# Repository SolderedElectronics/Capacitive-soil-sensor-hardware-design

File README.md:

# Capacitive soil sensor Hardware Design

## About the Product

|  |
| :----------------------------------------------------------: |
| [Buy Capacitive soil sensor](https://www.solde.red/333098) |

How many times have you watered your plants and feared you overdid it? With the capacitive soil sensor, those worries are a thing of the past!

Most cheap soil sensors work on the resistance principle, where there are two prongs and the sensor measures the conductivity between them. They work fine at first, but eventually begin to oxidize due to the exposed metal. Even if they are gold plated! Due to oxidation, the resistance goes up and up, so you have to constantly recalibrate your code. Also, resistance measurements do not always work in loose soil.

This design with capacitive measurement is superior. Capacitive measurements use only one prong, have no exposed metal, and do not introduce direct current into your plants.

---

## Repository Contents

This repository contains all design files for Capacitive soil sensor, organized as follows:

- **`CAD` folder**: Contains KiCAD design files, including:
  - Schematics
  - PCB layout
  - Panel PCB layout
  - Source 3D files in Fusion360, if any
  - All files are sorted by version with a detailed change log.
- **`OUTPUTS` folder**: Includes all production-ready files, such as:
  - Bill of Materials (BOM) and interactive BOM (iBOM)
  - PDF versions of schematics
  - 3D `.step` file of the board
  - 3D-printable models
  - Gerber files for PCB manufacturing
  - Image of the pinout of the board
  - Product image
  - Compliance, legal and generic sales documents

Refer to the `Change Log` in the CAD folder for details about updates between versions.

---

## Learn More About the Product

Beyond the repository, explore the following resources:

### Soldered Verify

The **Soldered Verify** system ensures every board you purchase from Soldered is fully functional. It also provides access to exclusive test data for your product. To get started, find the unique Soldered Verify ID on your product's packaging and enter the ID on the [Soldered Verify page](https://soldered.com/verify/) to access test results and additional product details.

### Soldered Community

Soldered Community is your go-to place for technical support. Our engineers track and answer all questions posted there, and it’s a great space for the maker community. Get answers to your questions and solutions for your challenges at [Soldered Community](https://soldered.com/community).

### solde.red

solde.red is an ultimate URL shortener and information hub. Access it by typing solde.red/ followed by your product SKU, e.g., [solde.red/333000](https://solde.red/333000), to find getting-started guides, datasheets, open-source hardware and software files, certifications, images, pinouts, and more. Read more about the shortener [here](https://solde.red/info/).

---

## Contributing

Contributions are welcome! Here’s how you can get involved:

- Submit pull requests to enhance the design or fix issues.
- Report bugs or problems by opening an issue.

We encourage community collaboration to make this product even better.

---

## About Soldered

[Soldered for Makers](https://soldered.com) specializes in designing and manufacturing electronic products tailored for enthusiasts, ranging from hobbyists to professionals. Our portfolio includes electronic boards, sensors, and actuators that are widely utilized in fields such as microelectronics, mechatronics, robotics, programming, and IoT. Every product we offer is designed in-house and built upon open-source hardware and software platforms. Proudly certified and manufactured within the European Union, our catalog likely includes the product you need for your project.

We complement these products with comprehensive tutorials and manuals, product descriptions, schematics, programming codes, and project examples. Our round-the-clock [customer and technical support](https://soldered.com/community) is available for all our products, irrespective of the sales channel. Soldered’s success and services reflect our maker community’s unwavering [trust](https://www.trustpilot.com/review/soldered.com), for which we are deeply grateful. Join our community and create using Soldered products.

---

## License

All Soldered open-source hardware (OSH) is under The TAPR Open Hardware License. Read more in the LICENSE file located in this repository.

**Disclaimer:**

No warranty - all designs in this repository are distributed in the hope that they will be useful, but without any warranty. They are provided "AS IS", therefore without warranty of any kind, either expressed or implied. The entire quality and performance of what you do with the contents of this repository are your responsibility. In no event Soldered Electronics will be liable for your damages, or losses, including any general, special, incidental, or consequential damage arising out of the use or inability to use the contents of this repository. 

---

## Have fun!

Thank you for your support from your fellow makers at Soldered Electronics.

Happy Making!

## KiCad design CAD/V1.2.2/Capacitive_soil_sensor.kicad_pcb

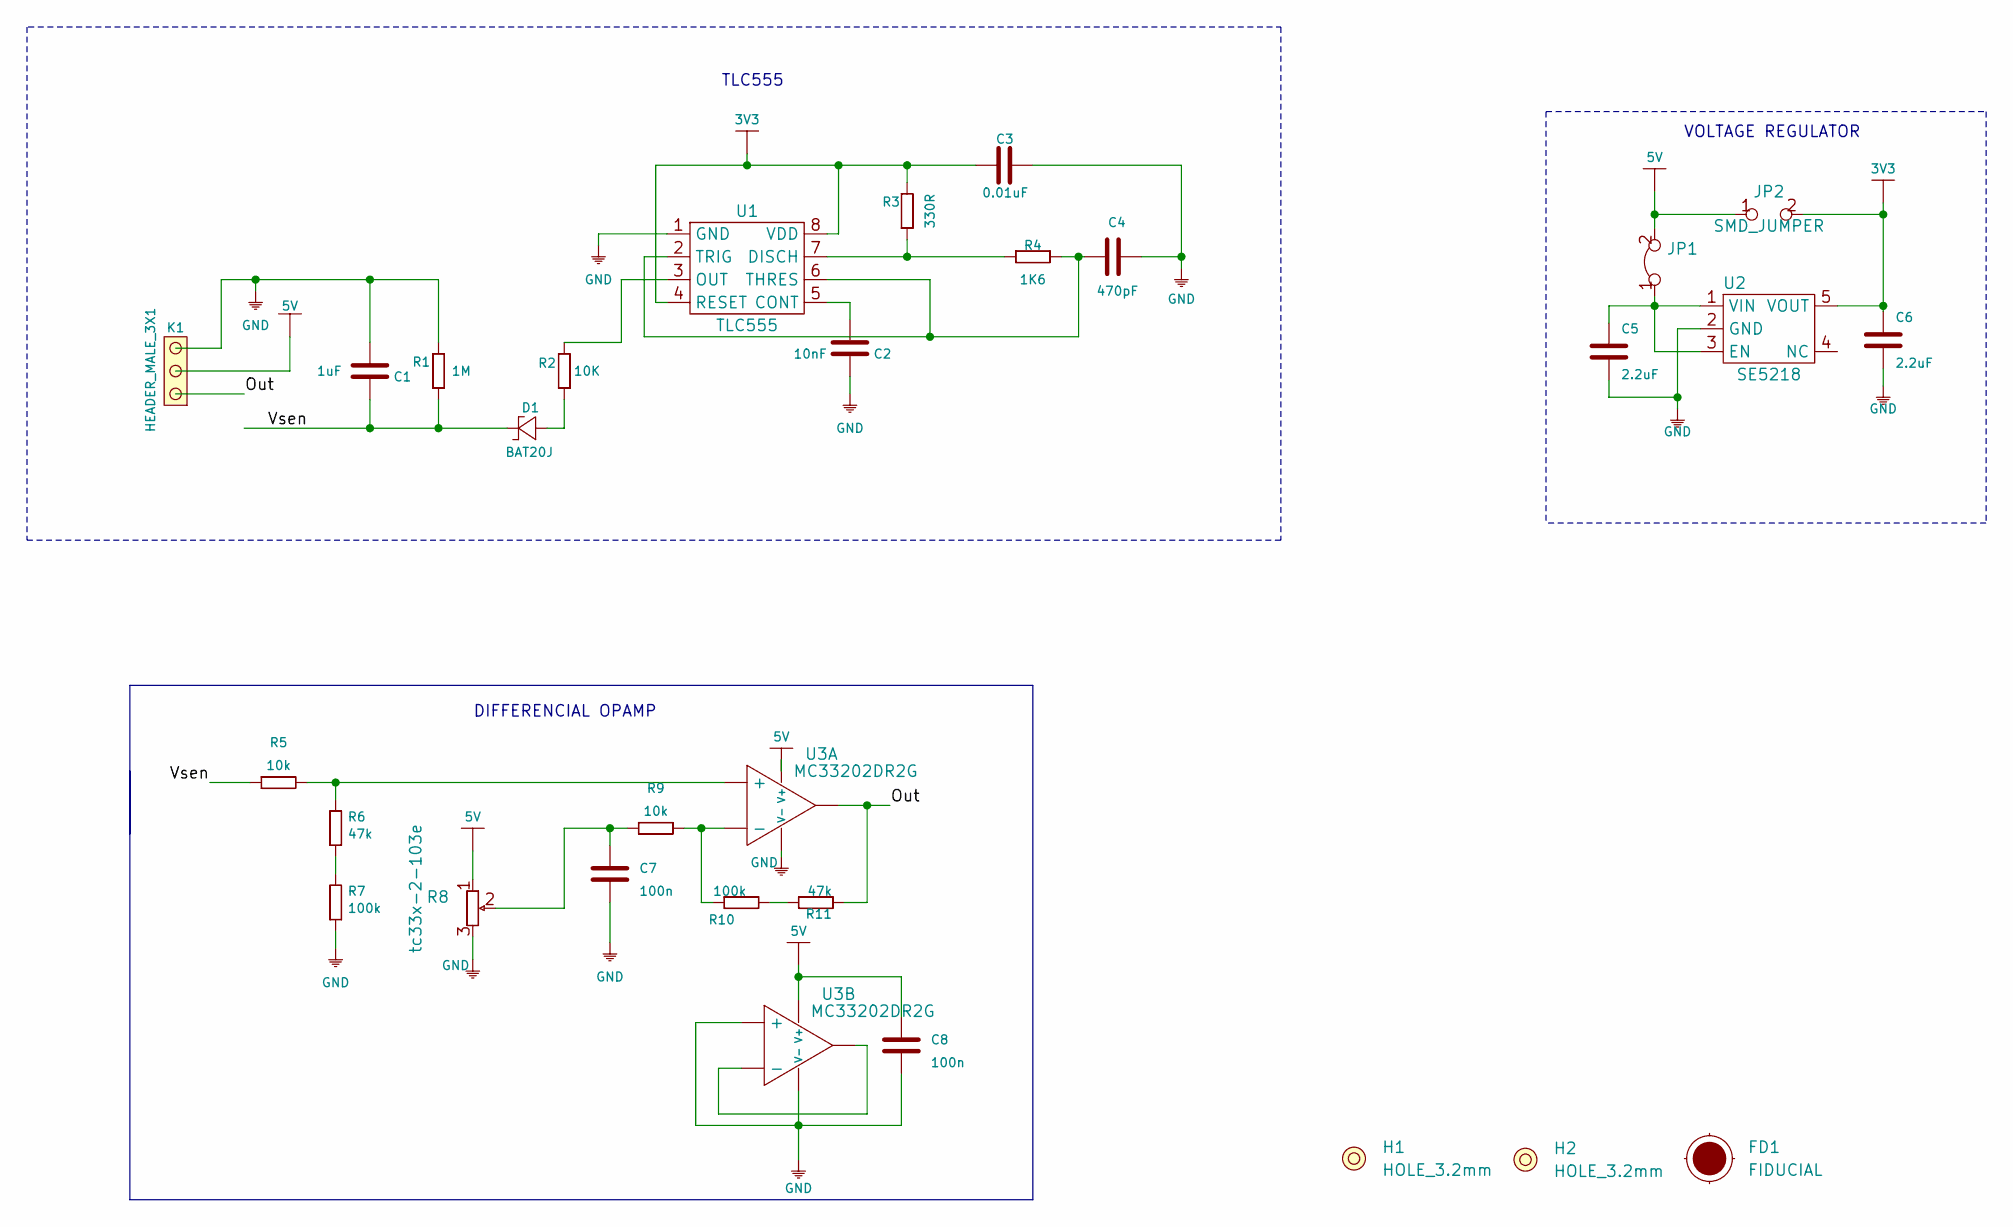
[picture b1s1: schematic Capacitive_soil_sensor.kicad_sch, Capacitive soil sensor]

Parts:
C1: 1uF; 0603C
C2: 10nF; 0603C
C3: 0.01uF; 0603C
C4: 470pF; 0603C
C5, C6: 2.2uF; 0603C
C7, C8: 100n; 0603C
D1: BAT20J; SOD-323
FD1: FIDUCIAL; FIDUCIAL_23
H1, H2: HOLE_3.2mm
JP1: SMD-JUMPER-CONNECTED_TRACE_SLODERMASK
JP2: SMD_JUMPER
K1: HEADER_MALE_3X1
R1: 1M; 0603R
R2: 10K; 0603R
R3: 330R; 0603R
R4: 1K6; 0603R
R5, R9: 10k; 0603R
R6, R11: 47k; 0603R
R7, R10: 100k; 0603R
R8: tc33x-2-103e
U1: TLC555; SOIC−8
U2: SE5218; SOT-23-5
U3: MC33202DR2G; SOIC−8

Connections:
3V3: C3.2, C6.2, JP2.2, R3.2, U1.4 (RESET), U1.8 (VDD), U2.5 (VOUT)
5V: C8.1, JP1.2, JP2.1, K1.2, R8.1, U3.8 (V+)
/Out: K1.1, R11.2, U3.1
/Vsen: C1.1, D1.2 (K), R1.1, R5.1
GND: C1.2, C2.1, C3.1, C4.1, C5.1, C6.1, C7.2, C8.2, K1.3, R1.2, R7.1, R8.3, U1.1 (GND), U2.2 (GND), U3.4 (V-), U3.5 (+)
unnamed: C2.2, U1.5 (CONT)
unnamed: C4.2, R4.2, U1.2 (TRIG), U1.6 (THRES)
unnamed: C5.2, JP1.1, U2.1 (VIN), U2.3 (EN)
unnamed: C7.1, R8.2, R9.1
unnamed: D1.1 (A), R2.1
unnamed: R2.2, U1.3 (OUT)
unnamed: R3.1, R4.1, U1.7 (DISCH)
unnamed: R5.2, R6.2, U3.3 (+)
unnamed: R6.1, R7.2
unnamed: R9.2, R10.1, U3.2 (-)
unnamed: R10.2, R11.1
unnamed: U3.6 (-), U3.7

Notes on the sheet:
DIFFERENCIAL OPAMP
VOLTAGE REGULATOR
TLC555

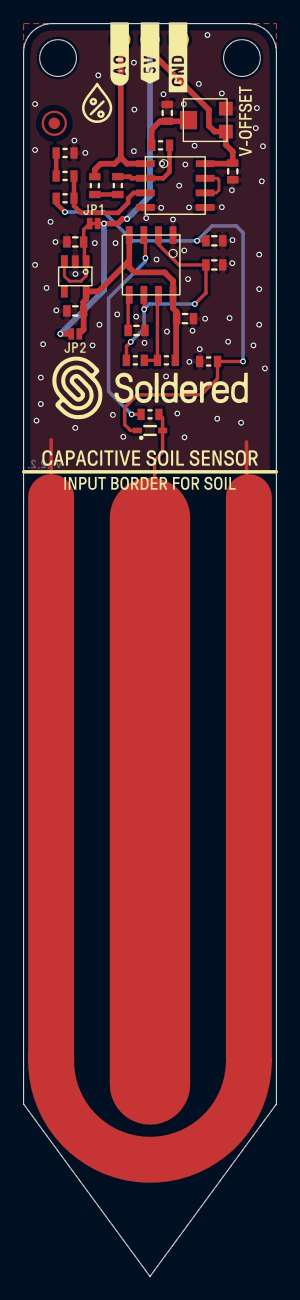
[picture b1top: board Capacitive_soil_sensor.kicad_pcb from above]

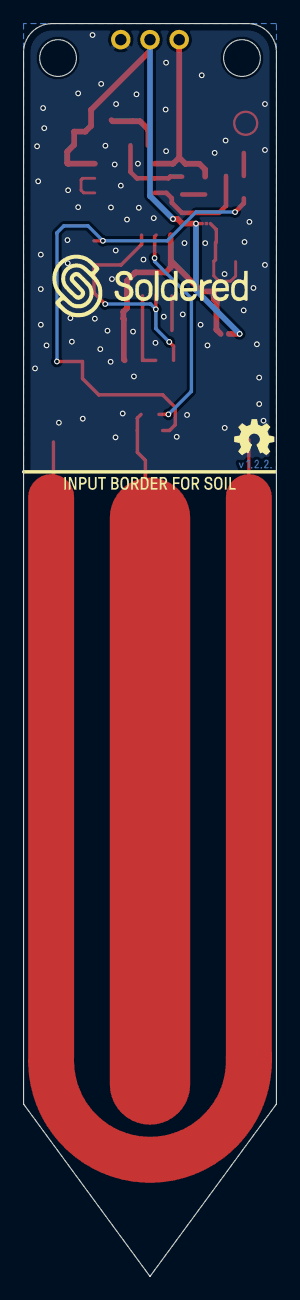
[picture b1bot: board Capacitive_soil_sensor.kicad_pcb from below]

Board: 2 copper layers, 22.0 x 109.0 mm, 33 parts (2 on the bottom side), 17 nets.

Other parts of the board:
kibuzzard-623B1C7E: G***; kibuzzard-623B1C7E
kibuzzard-6305B80A: G***; kibuzzard-6305B80A
kibuzzard-6305B93F, kibuzzard-6305B93F#2: G***; kibuzzard-6305B93F

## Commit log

2024-10-20 Updating open source files.
